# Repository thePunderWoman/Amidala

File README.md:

<p align="center">

</p>

**Amidala** is an ESP32-S3 firmware for controlling your droids. It runs on the [Amidala PCB](PCB/) — a PCB designed to make wiring a full-featured droid build straightforward — and is compatible with both the N8R2 (8 MB flash) and N16R8 (16 MB flash) module variants. Amidala is designed to pair with [Snips Controllers](https://github.com/thePunderWoman/SnipsControllers), coming soon, but can work with older Stealth controllers, bluetooth, or RC.

> **Building from source?** Flash size and PSRAM mode are baked into the firmware image at build time, so you need to tell PlatformIO which module your board has *before* your first flash — it can't be changed later via the web UI. Check the label on your ESP32-S3 module (or your PCB order) for "N8R2" or "N16R8", then build/upload with the matching environment: `pio run -e esp32s3-n16r8 -t upload` (the default) or `pio run -e esp32s3-n8r2 -t upload`. Just want to flash a droid rather than develop firmware? The **Firmware Installer** wizard below flashes a prebuilt image over USB — no toolchain needed.

> **[Amidala Wizards →](https://thepunderwoman.github.io/Amidala/)** — browser-based tools for setting up your droid. Includes a **Firmware Installer** for flashing prebuilt firmware over Web Serial, and a **Config Converter** for migrating Stealth RC / OG Amidala configs to the current format.

---

## Features

- **XBee wireless control** — secure, long-range, low-latency control via XBee 3 modules
- **Multiple Controller Support** — works with Snips Controllers (currently in prototype stage), classic stealth controllers, standard Bluetooth gamepads, and analog RC (PPM) input.
- **Wi-Fi configuration UI** — browser-based interface for fully configuring your droid without needing to pull the SD card.
- **WCB mesh networking** — join a [WCB](https://github.com/greghulette/WCBClient) ESP-NOW mesh to coordinate commands across multiple boards (e.g. a separate body controller) with no extra wiring.
- **Native HCR support** — full Human Cyborg Relations vocalizer integration, whether the HCR is wired straight to the board or owned by a WCB running its native HCR mode (Audio page → Serial Configuration).
- **Built in Serial Monitor** — full featured onboard native serial monitor to view traffic in real time, even across your WCB Mesh.
- **Advanced Dome Drive** — Built-in support for auto dome drive with a Pololu encoder motor and hall sensor, or any other basic PWM dome drive.
- **Flexible drive systems** — PWM, Sabertooth serial, or RoboteQ (PWM, serial, or hybrid)
- **Native built-in safety features** — Web based e-stop, dome obstruction motor disconnect, auto motor disable on controller disconnect.
- **Layers of controller button configurations** — with short-press, double-press, long-press, and alt-modifier layers
- **Effectively unlimited serial strings and gestures** — the only limits are your imagination!
- **Reassignable GPIO pin roles** — trade any of the board's digital output, analog input, PPM, or servo headers for another role right from the web UI (e.g. give up a digital output for a 5th servo channel), no reflashing needed
- **Reassignable dome/drive serial ports** — move the dome drive or drive system's serial link (RoboClaw, Sabertooth, RoboteQ serial) onto either of the board's two hardware UARTs from the web UI, for wiring that doesn't match the reference PCB or to free up a header for other hardware
- **And more** — I2C aux output, digital outputs, analog inputs, SD card config, servo outputs, and emergency stop handling

---

## Controller Support

Amidala is natively designed to work with [Snips Controllers](https://github.com/thePunderWoman/SnipsControllers) or other XBee-based dual handheld pocket controllers. It can also be used with standard Bluetooth controllers and RC.

## Web Configuration UI

The Amidala web interface allows you total control over your droid's configuration. You can set up your controller configuration, which buttons trigger what, add serial commands, set defaults for audio, dome positioning, safety timeouts, emergency stop commands, configure Bluetooth, see digital pin statuses, use the serial monitor, configure your droid's gadgets, and even use the droid control page to trigger sequences, trigger emotes, and dome controls. See more in the wiki.

## Availability and Pricing

Amidala boards are currently available to beta testers. Please let me know if you would prefer to have it pre-soldered or bare. Either way, it will come with the headers, slots, jumper, and power terminals. The ESP32-S3-N16R8 is standard and can be sourced from your favorite location. You will also need an XBee3 module if you intend to use Snips or Stealth controllers with your build. See the Wiki page for details on the recommended options. Price is $30 per board plus shipping, which includes a small donation to charity. Note: This does __not__ include controllers. However, once Snips Controllers are past the prototype phase, we will offer them together with Amidala.

Please reach out if you are interested in helping beta test.

## Get Started

> **[Documentation Wiki →](https://github.com/thePunderWoman/Amidala/wiki)**

The wiki covers everything from first flash through full configuration. For a quick look at every available config key, see [example_config.txt](example_config.txt) — it's a complete annotated reference used on a real build. Although once you get set up initially, you won't need to look at this file again, as you can update every config option through the web UI.

---

## The Amidala PCB

The Amidala PCB is a purpose-built carrier for the ESP32-S3, designed to consolidate all the connectors a typical R2 build needs onto a single board:

- 4 servo headers (LEDC PWM)
- 4 digital output pins
- 2 analog inputs
- 3 serial headers (UART0 primary out, plus UART1 and UART2 for the dome drive and drive system's serial link — reassignable between the two, see below)
- Auxiliary I2C header
- Native XBee slot (SPI, no adapter needed)
- Micro SD card reader
- Additional SPI breakout
- PPM input for RC receivers

> The servo, digital output, analog input, and PPM header counts above are just the defaults — each of those 11 pins can be independently reassigned to a different role from the web UI's Pins page (e.g. trade a digital output for a 5th servo channel, up to the ESP32-S3's 8-channel PWM ceiling). A reboot applies the change; no reflashing or rewiring of the PCB itself is needed.
>
> Likewise, UART1 and UART2 default to the dome drive and drive system's serial link respectively (matching the reference wiring), but either can be reassigned to the other from the web UI's Serial Ports page — e.g. if your build's wiring swaps which header the RoboClaw is actually connected to. UART0 always carries the primary serial-out / WCB mesh path and isn't reassignable.

> **[PCB details, Stackup circuit design, and BOM →](PCB/)**

---

## License

This project is released under the [GNU General Public License v2](LICENSE). You are free to use, modify, and distribute it — including your own modifications — as long as you share the source code of any distributed derivatives under the same license.

---

## Contributing

Bug reports and feature requests are welcome — please use the [issue tracker](https://github.com/thePunderWoman/Amidala/issues).

If you'd like to contribute code, see [CONTRIBUTING.md](CONTRIBUTING.md).

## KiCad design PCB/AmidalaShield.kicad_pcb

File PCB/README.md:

# AmidalaBoard (AmidalaShield)

A custom KiCad PCB shield designed specifically for the [Amidala Firmware](https://github.com/thePunderWoman/AmidalaFirmware) — a control system for astromech and similar droid builds. This board provides all the I/O the firmware needs in a single, purpose-built package.

**Designed by [thePunderWoman](https://github.com/thePunderWoman)**

The electrical design is written in [Stackup KDL](stackup/board.kdl), using the pinned
Stackup parts library plus [board-specific parts](stackup/parts.kdl). The
[KiCad PCB](AmidalaShield.kicad_pcb) is linked to it through `AmidalaShield.stackup_sch`;
sync it with the Stackup KiCad plugin after changing the design. See
[stackup/README.md](stackup/README.md).

---

## Overview

The AmidalaShield is a carrier/breakout board for the **ESP32-S3 N16R8 DevKit**. It breaks out and conditions the ESP32-S3's peripherals for the specific needs of the Amidala Firmware: wireless XBee communication, multi-channel servo control, RC receiver input, SD card storage, and expansion headers for additional peripherals.

---

## Requirements

- **Microcontroller:** ESP32-S3 N16R8 DevKit (16 MB flash, 8 MB PSRAM)
- **Wireless modules:** XBee3 modules (x2 recommended — one for drive controller, one for dome controller)

---

## Hardware Features

### Wireless Communication
- **XBee3 module socket** for dual-controller operation (drive + dome)

### Servo Control
- **4× PWM servo outputs** — 3-pin headers (signal, power, ground)

### Serial Ports
- **3× hardware serial ports** — UART0 (shared with USB/programming, silkscreen "Serial 0"), UART1 ("Serial 1"), and UART2 ("Serial 2"). None of these are bit-banged/software serial — the ESP32-S3's UART peripherals route through its GPIO matrix onto whichever pins are needed, unlike chips with a single hardware UART. Firmware reassigns the dome drive and drive system's serial link between Serial 1/Serial 2 at runtime — see the Amidala firmware wiki's [Serial Ports](https://github.com/thePunderWoman/Amidala/wiki/Serial-Ports) page.

### I/O
- **4× digital I/O pins**
- **2× analog input pins**
- **1× Aux I2C header** — for external I2C devices

### RC Control
- **PPM input (ppmin)** — for analog RC receiver

### Storage
- **Built-in microSD card reader** — used for `config.txt` at startup (matches Amidala Firmware config system)

### Expansion
- **Dedicated SPI header** — for external SPI peripherals

---

## Repository Contents

| File/Folder | Description |
|---|---|
| `stackup/board.kdl` | Electrical design (Stackup KDL), replacing the KiCad schematics |
| `stackup/parts.kdl` | Parts the Stackup library doesn't have (DevKitC, microSD socket, screw terminal, 3-way jumper) |
| `AmidalaShield.kicad_pcb` | PCB layout, synced from the Stackup design |
| `gerbers/` | Production-ready Gerber files |
| `libraries/` | Project-specific KiCad symbol/footprint libraries |
| `images/` | Board renders and screenshots |

---

## Getting Started

1. Clone this repo and open `AmidalaShield.kicad_pro` in KiCad 8+.
2. Review the [Stackup design](stackup/board.kdl) and the GPIO table below for pin assignments before assembling.
3. Use the Gerber files in `gerbers/` to order PCBs from your preferred fab.
4. Flash your ESP32-S3 with the [Amidala Firmware](https://github.com/thePunderWoman/AmidalaFirmware).
5. Place a `config.txt` on the microSD card — see the firmware repo for a full annotated example.

---

## GPIO Table

> **V1.1** — Updated GPIO assignments for ESP32-S3 WROOM-1 N8R2/N16R2 (Quad flash/PSRAM).
> Avoid GPIO35–37 on R8 (Octal) variants. GPIO48 reserved for onboard RGB LED.

| Function | GPIO | DevKit Side | Notes |
|---|---|---|---|
| **SPI MOSI** | GPIO11 | Left | Native FSPI, shared bus |
| **SPI MISO** | GPIO13 | Left | Native FSPI, shared bus |
| **SPI SCK** | GPIO12 | Left | Native FSPI, shared bus |
| **SD Card CS** | GPIO10 | Left | |
| **XBee CS** | GPIO7 | Left | |
| **SPI Spare CS** | GPIO14 | Left | Exposed header |
| **XBee ATTN** | GPIO16 | Left | |
| **XBee SLEEP** | GPIO15 | Left | |
| **I2C SDA** | GPIO8 | Left | Native I2C default |
| **I2C SCL** | GPIO9 | Left | Native I2C default |
| **UART0 TX** | GPIO43 | Right | Shared w/ USB — do not use simultaneously. Silkscreen "Serial 0"; fixed, carries the main serial-out/WCB mesh path |
| **UART0 RX** | GPIO44 | Right | Shared w/ USB — do not use simultaneously |
| **UART1 TX** | GPIO17 | Right | Silkscreen "Serial 1". Reassignable between the dome/drive serial link (default: dome) |
| **UART1 RX** | GPIO18 | Right | |
| **UART2 TX** | GPIO21 | Right | Silkscreen "Serial 2". Real hardware UART, not software serial. Reassignable between the dome/drive serial link (default: drive) |
| **UART2 RX** | GPIO38 | Right | |
| **PPMIN** | GPIO47 | Right | |
| **Analog 1** | GPIO1 | Right | ADC1_0, WiFi-safe |
| **Analog 2** | GPIO2 | Right | ADC1_1, WiFi-safe |
| **Servo 1** | GPIO3 | Left | Strapping pin (JTAG source), safe after boot |
| **Servo 2** | GPIO4 | Left | |
| **Servo 3** | GPIO5 | Left | |
| **Servo 4** | GPIO6 | Left | |
| **Digital 1** | GPIO39 | Right | Goes HIGH after reset (not LOW like most GPIOs) |
| **Digital 2** | GPIO40 | Right | |
| **Digital 3** | GPIO41 | Right | |
| **Digital 4** | GPIO42 | Right | Transitions low on reset slightly slower |
| **RGB LED** | GPIO48 | Right | Reserved — onboard DevKit RGB LED |
| **NC** | GPIO8 | Left | Reserved |

### Pins Intentionally Avoided

| GPIO | Reason |
|---|---|
| GPIO0 | Strapping pin — boot mode |
| GPIO3 | Strapping pin — JTAG source (used for Servo 1, safe after boot) |
| GPIO19/20 | USB D-/D+ |
| GPIO26–32 | Internal SPI flash/PSRAM — never use |
| GPIO35–37 | Internal on Octal (R8) variants — safe on R2 only |
| GPIO45 | Strapping pin — VDD_SPI voltage |
| GPIO46 | Strapping pin |

---

## License

This hardware design is licensed under the [Creative Commons Attribution-NonCommercial-ShareAlike 4.0 International License](LICENSE.md) (CC BY-NC-SA 4.0).

You are free to share and adapt this design for non-commercial purposes, as long as you give appropriate credit and distribute any adaptations under the same license.

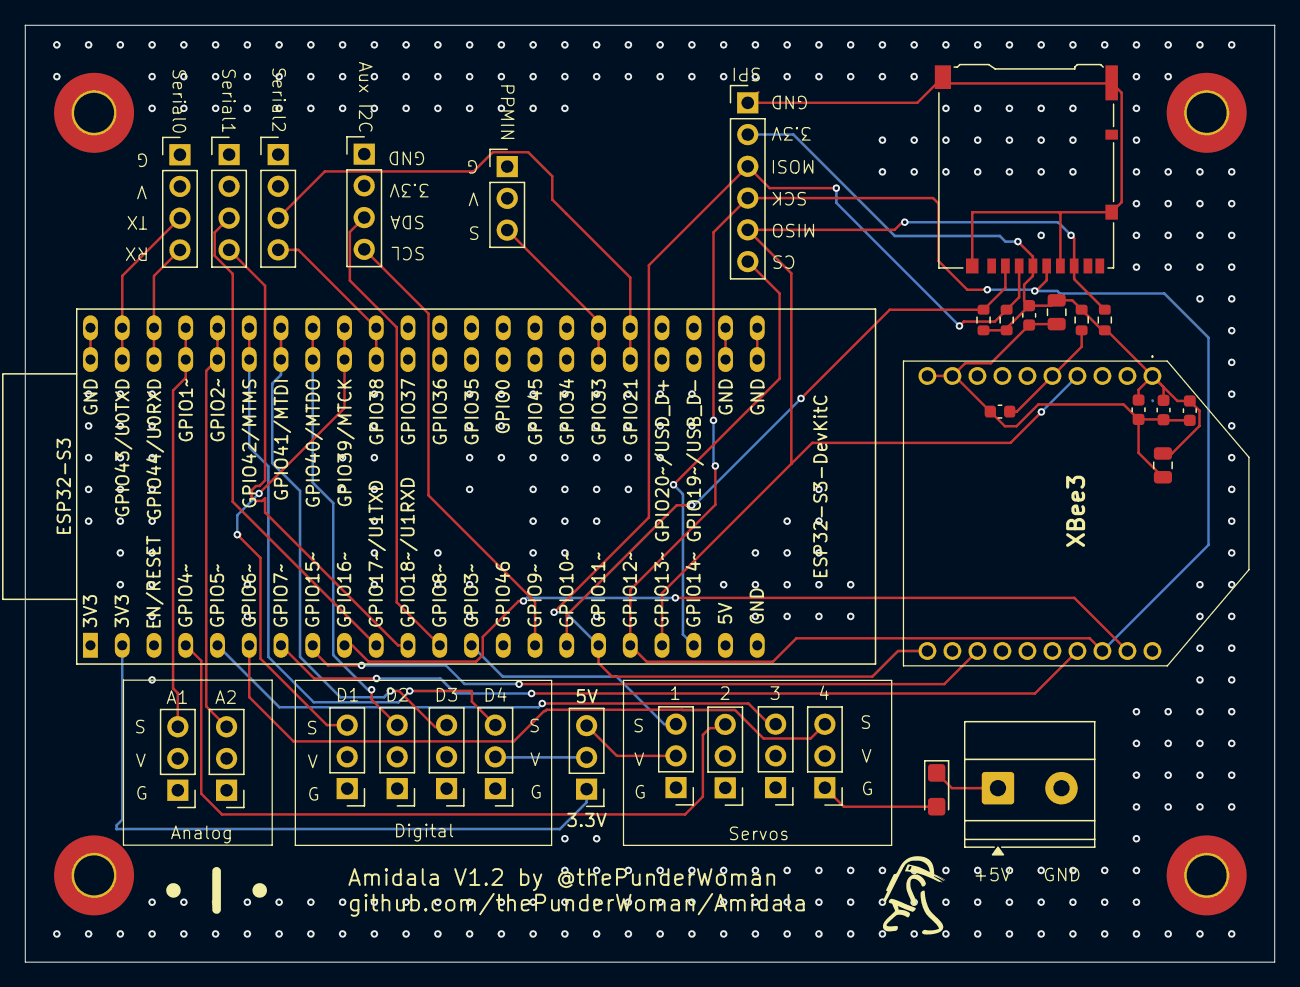
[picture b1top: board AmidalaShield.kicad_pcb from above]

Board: 4 copper layers, 99.9 x 74.9 mm, 33 parts (0 on the bottom side), 32 nets.

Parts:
C1, C2, C3: 100nF; C_0603_1608Metric
C4, C7: 10µF; C_0805_2012Metric
C5: 1µF; C_0603_1608Metric
C6: 8.2pF; C_0603_1608Metric
C9: 100µF; CP_EIA-3216-18_Kemet-A
ESP32-S3: ESP32-S3-DevKitC; ESP32-S2-DevKitC-1
I2C1: Aux I2C; PinHeader_1x04_P2.54mm_Vertical
J1: Screw_Terminal_01x02; TerminalBlock_Phoenix_MKDS-1,5-2-5.08_1x02_P5.08mm_Horizont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
J3: Micro_SD_Card; microSD_HC_Hirose_DM3AT-SF-PEJM5
JP1: Jumper_3_Open; PinHeader_1x03_P2.54mm_Vertical
J_Analog1: A1; PinHeader_1x03_P2.54mm_Vertical
J_Analog2: A2; PinHeader_1x03_P2.54mm_Vertical
J_Digital1: D1; PinHeader_1x03_P2.54mm_Vertical
J_Digital2: D2; PinHeader_1x03_P2.54mm_Vertical
J_Digital3: D3; PinHeader_1x03_P2.54mm_Vertical
J_Digital4: D4; PinHeader_1x03_P2.54mm_Vertical
J_PPMIN1: PPMIN; PinHeader_1x03_P2.54mm_Vertical
J_Servo1: 1; PinHeader_1x03_P2.54mm_Vertical
J_Servo2: 2; PinHeader_1x03_P2.54mm_Vertical
J_Servo3: 3; PinHeader_1x03_P2.54mm_Vertical
J_Servo4: 4; PinHeader_1x03_P2.54mm_Vertical
R1, R2, R3, R5: 10kΩ; R_0603_1608Metric
SPI1: SPI; PinHeader_1x06_P2.54mm_Vertical
SWSerial1: Serial2; PinHeader_1x04_P2.54mm_Vertical
Serial0: Serial0; PinHeader_1x04_P2.54mm_Vertical
Serial1: Serial1; PinHeader_1x04_P2.54mm_Vertical
XBee3: XB3-24Z8UT-J; XB324Z8UTJ

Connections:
+3.3V: C2.1, C3.1, C4.1, C5.1, C6.1, C7.1, ESP32-S3.1 (3V3), ESP32-S3.2 (3V3), I2C1.2, J3.4 (VDD), JP1.1 (A), J_PPMIN1.2, R1.1, R2.1, R3.1, R5.1, SPI1.2, SWSerial1.2, Serial0.2, Serial1.2, XBee3.1 (VCC)
+5V: C9.1, ESP32-S3.21 (5V), J1.1, JP1.3 (B), J_Servo1.2, J_Servo2.2, J_Servo3.2, J_Servo4.2
/Comms/GPIO8: ESP32-S3.12 (GPIO8/ADC1_CH7), I2C1.3
/Comms/GPIO9: ESP32-S3.15 (GPIO9/ADC1_CH8), I2C1.4
/Comms/GPIO17: ESP32-S3.10 (GPIO17/ADC2_CH6), Serial1.3
/Comms/GPIO18: ESP32-S3.11 (GPIO18/ADC2_CH7), Serial1.4
/Comms/GPIO21: ESP32-S3.27 (GPIO21), SWSerial1.3
/Comms/GPIO38: ESP32-S3.35 (GPIO38), SWSerial1.4
/Comms/GPIO43: ESP32-S3.43 (GPIO43/U0TXD), Serial0.3
/Comms/GPIO44: ESP32-S3.42 (GPIO44/U0RXD), Serial0.4
/Pins/GPIO1: ESP32-S3.41 (GPIO1/ADC1_CH0), J_Analog1.3
/Pins/GPIO2: ESP32-S3.40 (GPIO2/ADC1_CH1), J_Analog2.3
/Pins/GPIO39: ESP32-S3.36 (GPIO39/MTCK), J_Digital1.3
/Pins/GPIO40: ESP32-S3.37 (GPIO40/MTDO), J_Digital2.3
/Pins/GPIO41: ESP32-S3.38 (GPIO41/MTDI), J_Digital3.3
/Pins/GPIO42: ESP32-S3.39 (GPIO42/MTMS), J_Digital4.3
/RC Control/GPIO47: ESP32-S3.28 (GPIO47), J_PPMIN1.3
/SPI/GPIO7: ESP32-S3.7 (GPIO7/ADC1_CH6), XBee3.17 (AD3/DIO3/SPI_~SSEL)
/SPI/GPIO10: ESP32-S3.16 (GPIO10/ADC1_CH9), J3.2 (DAT3/CD), R2.2
/SPI/GPIO11: ESP32-S3.17 (GPIO11/ADC2_CH0), J3.3 (CMD), R3.2, SPI1.3, XBee3.11 (DIO4/SPI_MOSI)
/SPI/GPIO12: ESP32-S3.18 (GPIO12/ADC2_CH1), J3.5 (CLK), SPI1.4, XBee3.18 (AD2/DIO2/SPI_CLK)
/SPI/GPIO13: ESP32-S3.19 (GPIO13/ADC2_CH2), J3.7 (DAT0), R5.2, SPI1.5, XBee3.4 (DIO12/SPI_MISO)
/SPI/GPIO14: ESP32-S3.20 (GPIO14/ADC2_CH3), SPI1.6
/SPI/GPIO15: ESP32-S3.8 (GPIO15/ADC2_CH4/32K_P), XBee3.13 (ON/~SLEEP/DIO9)
/SPI/GPIO16: ESP32-S3.9 (GPIO16/ADC2_CH5/32K_N), XBee3.19 (AD1/DIO1/SPI_~ATTN)
/Servos/GPIO3: ESP32-S3.13 (GPIO3/ADC1_CH2), J_Servo1.3
/Servos/GPIO4: ESP32-S3.4 (GPIO4/ADC1_CH3), J_Servo2.3
/Servos/GPIO5: ESP32-S3.5 (GPIO5/ADC1_CH4), J_Servo3.3
/Servos/GPIO6: ESP32-S3.6 (GPIO6/ADC1_CH5), J_Servo4.3
GND: C1.2, C2.2, C3.2, C4.2, C5.2, C6.2, C7.2, C9.2, ESP32-S3.22 (GND), ESP32-S3.23 (GND), ESP32-S3.24 (GND), ESP32-S3.44 (GND), I2C1.1, J1.2, J3.6 (VSS), J3.11 (SHIELD), J_Analog1.1, J_Analog2.1, J_Digital1.1, J_Digital2.1, J_Digital3.1, J_Digital4.1, J_PPMIN1.1, J_Servo1.1, J_Servo2.1, J_Servo3.1, J_Servo4.1, SPI1.1, SWSerial1.1, Serial0.1, Serial1.1, XBee3.9 (~DTR/SLEEP_RQ/DIO8), XBee3.10 (GND)
unnamed: C1.1, R1.2, XBee3.5 (~RESET)
VCC_DIG: JP1.2 (C), J_Analog1.2, J_Analog2.2, J_Digital1.2, J_Digital2.2, J_Digital3.2, J_Digital4.2

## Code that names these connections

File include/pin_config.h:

// pin_config.h
// Hardware pin assignments and serial port mappings for Amidala Firmware.
// All physical I/O pin numbers and serial port aliases are defined here so
// that wiring changes require edits in exactly one place.
//
// Target: ESP32-S3 WROOM1 N16R8 — Amidala custom PCB v1.2.
//
// Note: RDH_SERIAL (see rdh_serial.h) must be resolved before this header is
// included — it shares Serial0's RX/TX pins with the SERIAL macro below.

#pragma once

// ---- Servo output pins (LEDC PWM via ServoDispatchESP32) --------------------
// 3 active channels: right drive, left drive, throttle. SERVO4 defined but unassigned.

#define SERVO1_PIN  3   // Drive Right
#define SERVO2_PIN  4   // Drive Left
#define SERVO3_PIN  5   // Throttle / speed-control
#define SERVO4_PIN  6

// ---- Digital output pins ----------------------------------------------------
// 4 channels on this PCB (v1.2).
// DRIVE_ACTIVE / DOME_ACTIVE are not wired; setDigitalPin() treats a 0 entry
// as absent.

#define DOUT1_PIN   39
#define DOUT2_PIN   40
#define DOUT3_PIN   41
#define DOUT4_PIN   42

// ---- Hall-effect sensor (RoboClaw dome drive) --------------------------------
// Wired to the Digital 2 header (GPIO40).  All ESP32-S3 GPIOs support
// external interrupts, so any digital pin would work here.

#define DOME_HALL_PIN  40

// ---- PPM RC input -----------------------------------------------------------

#define PPMIN_PIN   47

// ---- Analog inputs (ADC1, WiFi-safe) ----------------------------------------

#define ANALOG1_PIN  1   // ADC1_0
#define ANALOG2_PIN  2   // ADC1_1

// ---- SD card chip-select pin ------------------------------------------------

#define SD_CS_PIN   10

// ---- Serial1 (UART1 / Serial 1 header) --------------------------------------
// GPIO17 TX / GPIO18 RX. Real hardware UART1; explicit pins required since
// ESP32-S3 UART1 has no hardware-fixed default pins. Reassignable (issue
// #147) between the dome and drive serial links -- see serial_assignment.h.
// Historically only used by the RoboClaw dome (as ROBOCLAW_RX_PIN/TX_PIN in
// drive_config.h, same GPIOs) before reassignment existed.

#define SERIAL1_TX_PIN  17
#define SERIAL1_RX_PIN  18

// ---- AUX serial (UART2 / Serial 2 header) -----------------------------------
// GPIO21 TX / GPIO38 RX.  Always compiled in; enabled at runtime via auxserial3=.

#define AUX_SERIAL         Serial2
#define AUX_SERIAL_TX_PIN  21
#define AUX_SERIAL_RX_PIN  38

// ---- SPI bus pins -----------------------------------------------------------

#define SPI_MOSI_PIN      11
#define SPI_MISO_PIN      13
#define SPI_SCK_PIN       12
#define XBEE_CS_PIN        7
#define XBEE_ATTN_PIN     16
#define XBEE_SLEEP_PIN    15
#define SPI_SPARE_CS_PIN  14

// ---- I2C bus pins -----------------------------------------------------------

#define I2C_SDA_PIN  8
#define I2C_SCL_PIN  9


// ---- Serial port assignments ------------------------------------------------
// Serial  = USB-CDC console  (ARDUINO_USB_CDC_ON_BOOT=1)
// Serial0 = UART0 GPIO43/44  WCB / body controller out  (was Serial3 on Mega)
// Serial1 = UART1 GPIO17/18  RoboClaw dome drive         (see drive_config.h)
//
// Always pass explicit pin args to Serial0/Serial1.begin(): on ESP32-S3 the
// GPIO matrix routes UARTs to whatever pins you specify, and board-variant
// defaults may not match the Amidala PCB wiring.

#define SERIAL0_RX_PIN  44   // UART0 RX — WCB / body controller out
#define SERIAL0_TX_PIN  43   // UART0 TX

#define CONSOLE_SERIAL  Serial   // USB-CDC

// SERIAL (downstream WCB output) — ESP32 Arduino.h defines SERIAL as 0x0
// (a UART index constant).  Undefine it so we can use SERIAL as a Stream alias.
// DOME_DRIVE_SERIAL / DRIVE_SERIAL no longer need to suppress this: drive and
// dome serial links use AUX_SERIAL (UART2), not Serial0 — see
// drive_config.h. Only RDH_SERIAL, which shares Serial0's RX/TX pins (see
// AmidalaFirmware.ino), still genuinely conflicts.
#if !defined(RDH_SERIAL)
#undef  SERIAL
#define SERIAL  Serial0          // UART0, GPIO43/44 — WCB serial out
#endif

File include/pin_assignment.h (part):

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// Hardware ceilings enforced here:
//   - Servo <= 8: the ESP32-S3's LEDC peripheral has exactly 8 PWM channels,
//     full stop, regardless of how many pins are in the pool.
//   - Analog: only GPIO1-10 are ADC1-capable (WiFi-safe) on ESP32-S3; within
//     the pool that's {1,2,3,4,5,6}.
//   - PPM <= 1: there's a single PPMDecoder instance.
//   - Hall <= 1: there's a single dome hall-sensor input. Only meaningful
//     when DOME_DRIVE_ROBOCLAW is compiled in -- this header stays agnostic
//     of DOME_DRIVE (no #include of drive_config.h), so it's the caller's
//     job to decide whether to ever offer/use the Hall role at all. Hall
//     defaults to GPIO40 (this PCB's hall sensor trace) but is reassignable
//     if a user has physically rewired their hall sensor to a different pin.
//   - DOUT: no ceiling beyond the pool size -- plain digitalWrite() has no
//     hardware channel-count limit, unlike PWM/LEDC.
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// the entire assignable pool. Also the single source of truth for the web
// UI's per-pin rows (see buildFullConfigJson()'s "pinRoles"/pin list).
//
// GPIO3 (default role: Servo) is a JTAG-strapping pin, but it's already in
// production use as a PWM output today with no issue (Reeltwo's own
// ServoDispatchESP32::validPWM() has this exclusion commented out
// upstream) -- keeping it in the pool introduces no new risk, since it was
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//   - true (parsing config.txt at boot): only the per-pin check
//     (validateRoleForPin()). config.txt lines arrive in FILE order, not in
//     dependency order, so a ceiling check against a half-parsed array
//     rejects perfectly good configs -- e.g. a Hall move to GPIO39 is saved
//     as pin39role=hall (parsed first, while GPIO40 still holds its DEFAULT
//     Hall role) then pin40role=dout, and a strict check rejects the first
//     line, so the sensor snaps back to GPIO40 on every reboot. Ceilings are
//     enforced once, with the whole array in hand, by sanitizePinRoles()
//     (params.h) after the file is fully read.
inline PinRoleValidationResult applyPinRoleChange(PinRoleType allRoles[11], uint8_t pin,
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
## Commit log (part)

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2026-06-22 Board V1.2 minor polish
    This adds some graphics and ensures the board definitely comes in at just under the 100mm width mark for price benefits.
2026-06-25 Update readme note about wiki
    The wiki now exists and is not just coming soon.
2026-06-26 refactor: Update PCB with power jumper
    This adds a jumper to connect the digital and analog pins to either 3.3v or 5v depending on the jumper position.
